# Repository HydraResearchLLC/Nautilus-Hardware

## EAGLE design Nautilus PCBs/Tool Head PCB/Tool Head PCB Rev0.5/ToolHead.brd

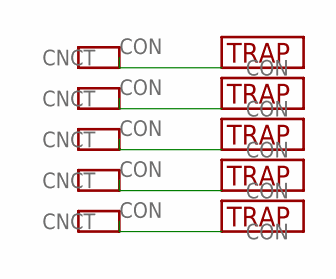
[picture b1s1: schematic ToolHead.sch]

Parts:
U$1, U$2, U$3, U$4, U$5: MOLEX-LITE-TRAP
U$6, U$7, U$8, U$9, U$10: SPRING-FINGER

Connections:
unnamed: U$4.TRAP, U$10.CON
unnamed: U$3.TRAP, U$9.CON
unnamed: U$2.TRAP, U$8.CON
unnamed: U$1.TRAP, U$7.CON
unnamed: U$5.TRAP, U$6.CON

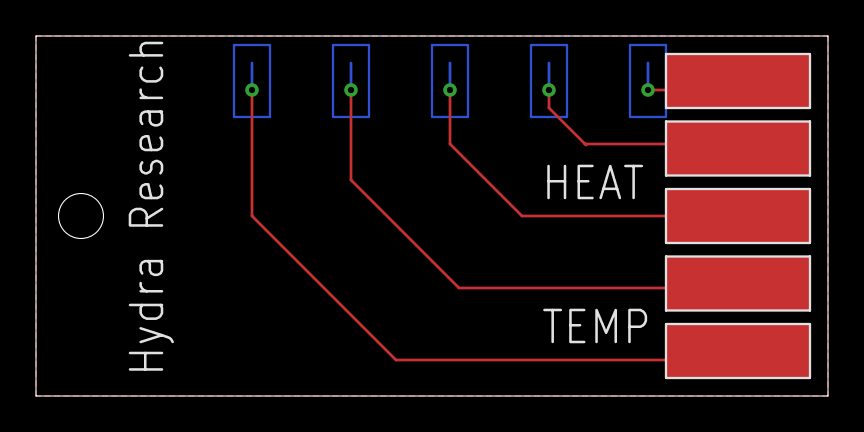
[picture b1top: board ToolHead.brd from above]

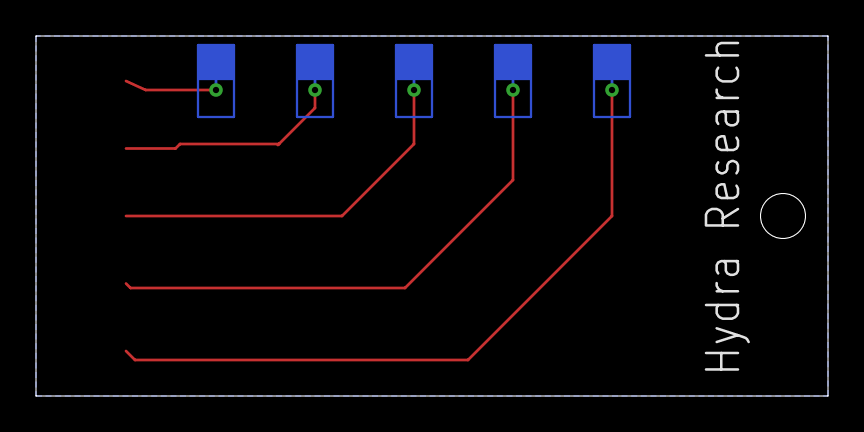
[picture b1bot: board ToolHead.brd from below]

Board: 2 copper layers, 44.0 x 20.0 mm, 10 parts (5 on the bottom side), 5 nets.

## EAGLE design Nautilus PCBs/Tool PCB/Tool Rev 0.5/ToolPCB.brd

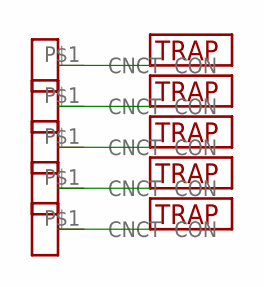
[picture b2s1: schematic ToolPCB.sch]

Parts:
U$1, U$2, U$3, U$4, U$5: MOLEX-LITE-TRAP
U$6, U$7, U$8, U$9, U$10: B_CONTACT

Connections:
unnamed: U$3.TRAP, U$6.P$1
unnamed: U$2.TRAP, U$7.P$1
unnamed: U$1.TRAP, U$8.P$1
unnamed: U$4.TRAP, U$9.P$1
unnamed: U$5.TRAP, U$10.P$1

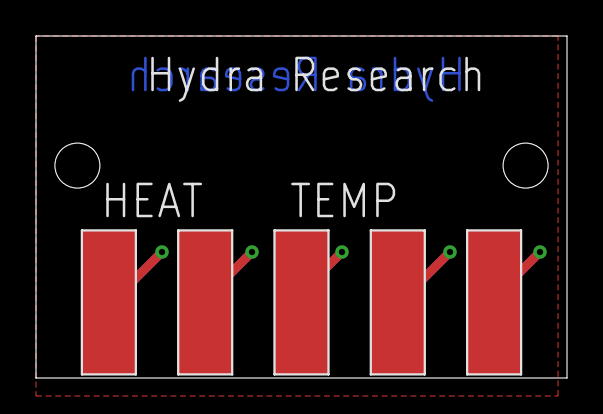
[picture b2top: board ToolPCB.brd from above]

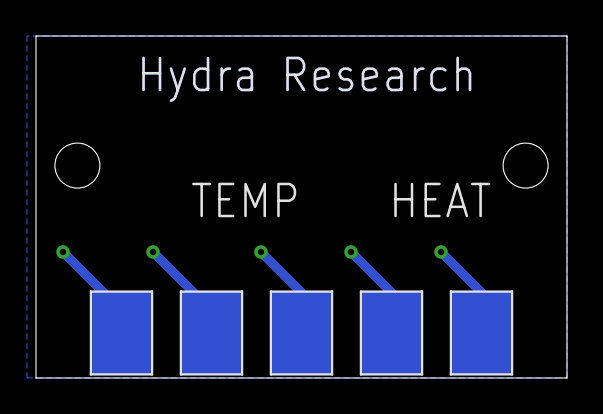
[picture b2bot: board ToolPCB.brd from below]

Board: 2 copper layers, 29.5 x 19.0 mm, 10 parts (5 on the bottom side), 5 nets.

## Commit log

2019-05-24 Initial Nautilus hardware upload to GitHub
2019-05-24 added more stuff
2019-05-24 updating stls
2019-06-13 updating files
2019-06-13 adding license
2019-06-13 renaming license files
2019-06-13 name change
2019-06-14 Adding LGPL
2019-06-29 updating hardware files before release
2019-10-19 adding fifth contact for tool PCB
2019-10-20 PCB Tool Head with five contacts
2019-10-23 updated PCBS with new parts 10-22-2019
2019-10-23 .gitignore update
